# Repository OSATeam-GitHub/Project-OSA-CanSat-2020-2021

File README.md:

#  Project OSA

OSA a is minisatellite/ space probe the size of a can designed to participate in the ESA CanSat 2021 competition 🛰️📡. Our project is called OSA (in Polish “Opadający Satelita Atmosferyczny” is loosely translated into “Falling Atmospheric Satellite”) and team - [OSATeam](https://www.osacan.eu/)

OSA is desgined to carry out reasearches while falling in the atmospehere. Space probe can be deployed from drone, rocket or droped from certain altitude. Parachute guarantees safe landing. Primarily device measures air temperature, pressure, humidity and send it via LoRa radio to the ground station. This data is used onboard sattelite to calculate live altitude. 

The main aim for OSA is to collect five air samples🧪 for later analysis. It is done by custom-designed mechanism, that injects needle to autosealing sterile containers and pump air sample into it. 

Among other OSA has built-in GPS so after lunch it can be found easily.

## Tabele of contents
* [Mechanical design](#mechanical-design)
* [Electronic design](#electronic-design)
* [OSA software](#osa-software)
* [Contact](#contact)
* [Licence](#licence)
## Mechanical design
Mechanical was designed in fusion 360. The full project is available to watch with this link:
https://a360.co/3AG3GMY. 
All parts which should be 3D printed are also available above. You should use precise printer. To print them we used high-quality PLA. Inaacuracy will yield in device inoperatavity. 

### Sting System
System injects needle into container using gear and slider powered by servomechanism. Then pump inflates atmosphere into the container. In fact there is to need to use pump due to fact containers are underpressure, although puting pump into system will increase concentartion of gases. Then upper part of sting system is rotated by carousele. 

### Carousele
The carousel is designed to turn the servo and sting. It uses a stepper motor and three gears (ratio 1:1:1). The
motor does not have a centered shaft, therefore a gear system consisting of three gears has been printed on a 3D
printer. Servo gear is located in the middle and it holds the servo. On one side there is motor gear that is attached
to the [28BYJ-48 stepper motor](https://botland.com.pl/silniki-krokowe/12807-silnik-krokowy-z-przekladnia-28byj-48-5v-01a-003nm-ze-sterownikiem-uln2003.html). On the opposite side, there is support gear that makes the mechanism work with lower
backlash. Carusele is part of main-base body. It might be challenging to print therefor we additionaly added splited main-base part. Printing spearetly should be easier, after printing that way the prats should be glued togather.
Servo gear is printed in place with the base of the case as one part. It is mounted on the round body, so
it holds together. Support gear is printed as a separate part. While the base is printing the printer should be stoped at the right
height so the support gear could be manually added ( the stoping point can be set in slicer ).

### Servo mechanism
The servo mechanism converts the rotation of the motor into linear movement of the needle therefore it can be injected into the test tube.
The blocker part is additionally added to help the needle stay in place.

### Main casing body and electronic case
Both the main casing body ( main-mid ) and the electronic case are designed to be printed without any supports. They don't require as high precision as the carousel does.

## Electronic design
OSA is powered by the CanSat kit, therefore it’s fully compatible with Arduino m0. Full CanSat kit documentation can be found on the ESERO Polska page in the statute, or right [here](https://github.com/CanSatKit/Documentation). On to the mainboard, you should sold GPS module as well as the  1/2 wave long antenna. [This](https://www.changpuak.ch/electronics/yagi_uda_antenna_DL6WU.php?fbclid=IwAR0hKYk1dh2FgNYhQmpAeVwOAlgjz0rPHka-r6Hd5ZqAI7iYF1GUxPW0EE0) calculator may be useful. 

Currently, we are working on a new PCB board for OSA. We will upload the design with the scheme soon.

### Ground station hardware
OSA ground station is simply the CanSat kit board connected with a yagi directional antenna. The mainboard should be connected by USB with PC or laptop.
It will work with any antenna which fulfils requirments (the closer to requitments the better signal:

- Frequency     :  433  MHz
- Wavelength    :  693  mm
- Rod Diameter  :  10  mm
- Boom Diameter :  20  mm
- Boom Length   :  238  mm
- d/lambda      :  0.014    ( min.: 0.002 , max.: 0.01 )
- D/lambda      :  0.029    ( min.: 0.01 , max.: 0.05 )
- Elements      :  3
- Gain          :  5.23 dBd (approx.)
- Reflector Length   : 334 mm
- Reflector Position :  0 mm
- Dipole Position    : 166 mm
- Director #1 Position : 218 mm ,  Length : 315 mm
- Distance Dipole - Dir. #1 : 52 mm 

[yagi antenna calculator](https://www.changpuak.ch/electronics/yagi_uda_antenna_DL6WU.php)

## OSA software
OSA OS is Arduino based. To make the code clean we wrote a library for controlling all OSA systems. 

Before launch, when OSA is turned on it will take measurements and calculation to establish ground altituted. Until detecting the opening of the parachute OSA will stay in the rest position. It means that the needle will be hidden between two probes so it takes less space. After detecting the opening of the parachute OSA waits about a second to stabilize and then sets current altitude as final altitude. Then it calculates five intervals on which it’s supposed to take the samples. 

Independently OSA takes measurements from all sensors every second, send it via radio and save it on SD card. Excluding pressure, temperature, humidity OSA equipped with a sensor that measures the pressure inside the pipe connected with the needle. According to that pressure we know whether the probe was taken or not. If for some reason any of the samples wasn’t taken, after taking all others OSA will come back and repeat taking those samples. OSA sends various data about the so not only do we know whether the sample was taken or not, but also exactly the altitude it started and finished taking. Also, the altitude at which the parachute was opened is saved.

OSA encodes data which is send via radio, otherwise buffor would have stucked. 

## Contact
📫 We are opened to suggestions and collaboration. Contact us!
- https://www.facebook.com/osacan.eu/
- https://www.instagram.com/osateam_cansat/
- osacansat@gmail.com
- @OSATeam_CanSat

## Licence
Copyright (C)  2020 Project OSA.

This project is free software and hardware: you can redistribute it and/or modify
    it under the terms of the GNU General Public License as published by
    the Free Software Foundation, either version 3 of the License, or
   any later version.

   This program is distributed in the hope that it will be useful,
    but WITHOUT ANY WARRANTY; without even the implied warranty of
    MERCHANTABILITY or FITNESS FOR A PARTICULAR PURPOSE.  See the
    GNU General Public License for more details.

   You should have received a copy of the GNU General Public License
    along with this program.  If not, see <https://www.gnu.org/licenses/>.
    
<!---
OSATeam-GitHub/OSATeam-GitHub is a ✨ special ✨ repository because its `README.md` (this file) appears on your GitHub profile.
You can click the Preview link to take a look at your changes.
--->

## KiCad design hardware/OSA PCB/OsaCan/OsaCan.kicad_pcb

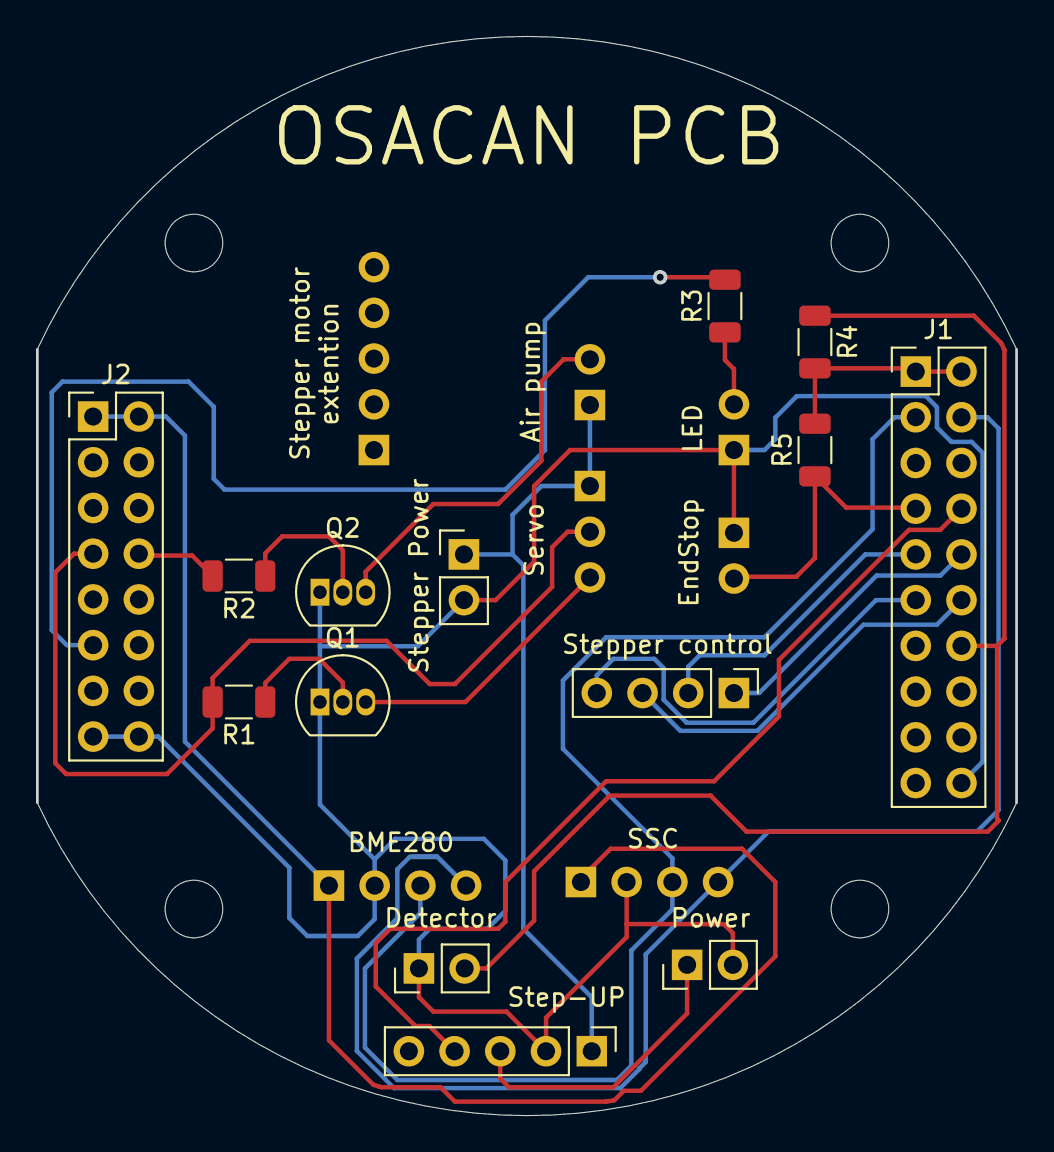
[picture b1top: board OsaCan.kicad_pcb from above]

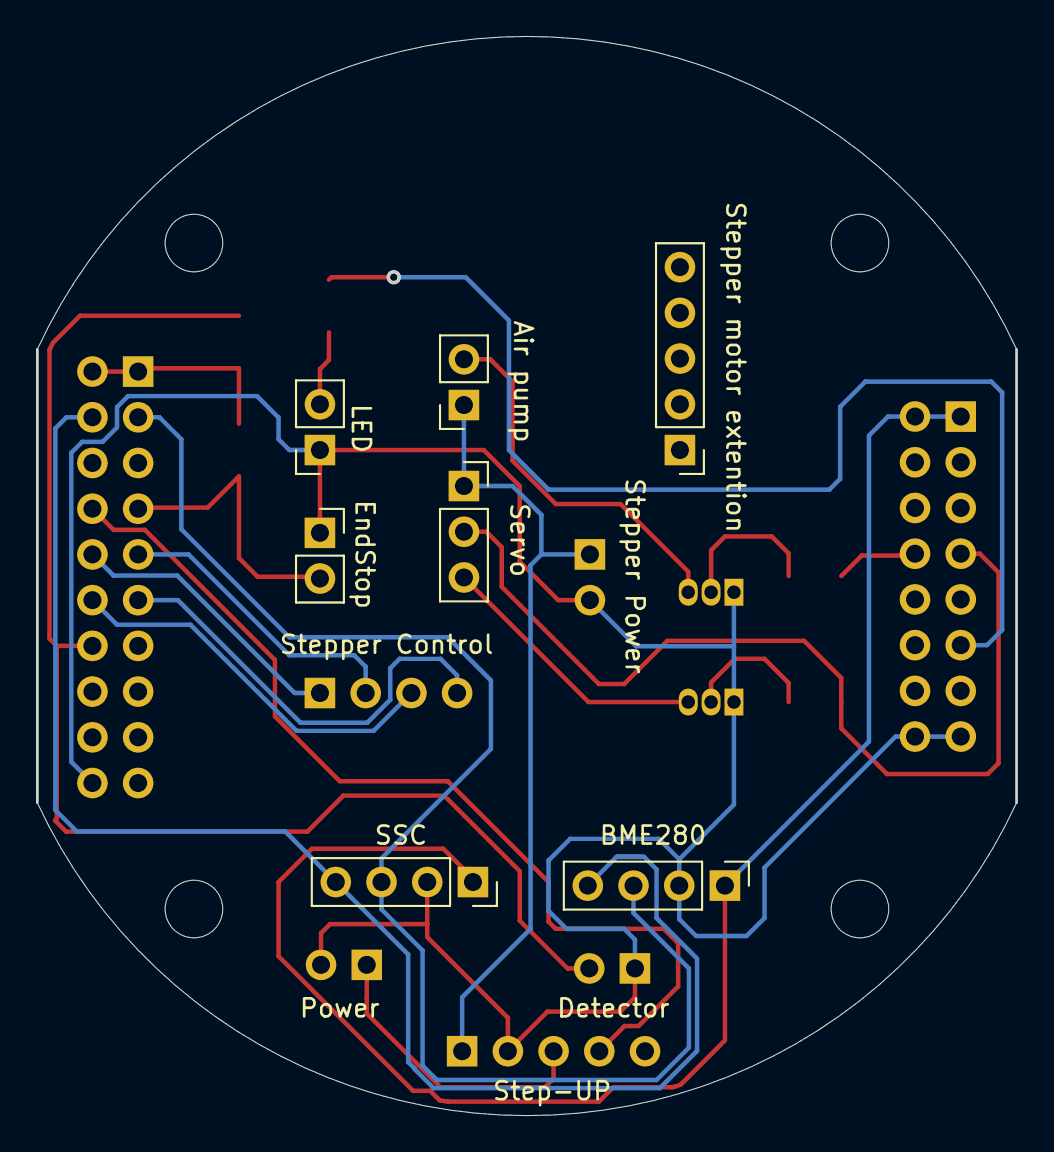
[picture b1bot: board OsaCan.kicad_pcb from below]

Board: 2 copper layers, 54.4 x 60.0 mm, 21 parts (7 on the bottom side), 22 nets.

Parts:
Air pump: Conn_01x02; PinSocket_1x02_P2.54mm_Vertical
BME280: BME_280; PinHeader_1x04_P2.54mm_Vertical
Detector: Detector; PinHeader_1x02_P2.54mm_Vertical
EndStop: EndStop; PinSocket_1x02_P2.54mm_Vertical
J1: Conn_02x10_Odd_Even; PinHeader_2x10_P2.54mm_Vertical
J2: Conn_02x08_Odd_Even; PinHeader_2x08_P2.54mm_Vertical
LED: Conn_01x02; PinSocket_1x02_P2.54mm_Vertical
Power: POWER; PinHeader_1x02_P2.54mm_Vertical
Q1, Q2: S8050; TO-92_Inline
R1, R2, R3, R4, R5: R; R_1206_3216Metric
SSC: ssc; PinSocket_1x04_P2.54mm_Vertical
Servo: Conn_01x03; PinSocket_1x03_P2.54mm_Vertical
Step-UP: Step-up; PinHeader_1x05_P2.54mm_Vertical
Stepper Power: Stepper Power; PinHeader_1x02_P2.54mm_Vertical
Stepper control: Stepper Motor; PinHeader_1x04_P2.54mm_Vertical
Stepper motor extention: Stepper pin extention; PinHeader_1x05_P2.54mm_Vertical

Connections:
+3V3: BME280.1, J2.1, J2.2, SSC.1
+4V: Power.1, Step-UP.3
+5V: J1.1, J1.2, R4.2, R5.2
+6V: Air pump.1, Servo.1, Step-UP.1, Stepper Power.1
A0: Detector.2, J1.14, R4.1
D0: J1.8, Step-UP.4
D1: EndStop.2, J1.7, R5.1
D2: J1.10, Stepper control.1
D3: J1.9, Stepper control.2
D4: J1.12, Stepper control.3
D5: J1.11, Stepper control.4
D6: J2.7, R1.2, Servo.2
D7: J2.8, R2.2
D13: J2.11, R3.2
GND: BME280.2, Detector.1, EndStop.1, J1.20, J2.15, J2.16, LED.1, Power.2, Q1.1, Q2.1, SSC.2, Step-UP.2, Stepper Power.2
unnamed: Air pump.2, Q2.3
unnamed: LED.2, R3.1
unnamed: Q1.2, R1.1
unnamed: Q1.3, Servo.3
unnamed: Q2.2, R2.1
SCL: BME280.3, J1.3, SSC.3
SDA: BME280.4, J1.4, SSC.4

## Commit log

2021-09-05 Create LICENSE
